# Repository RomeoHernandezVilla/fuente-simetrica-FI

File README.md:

# fuente_simetrica_FI
 HW pininos fuente de alimentacion simetrica

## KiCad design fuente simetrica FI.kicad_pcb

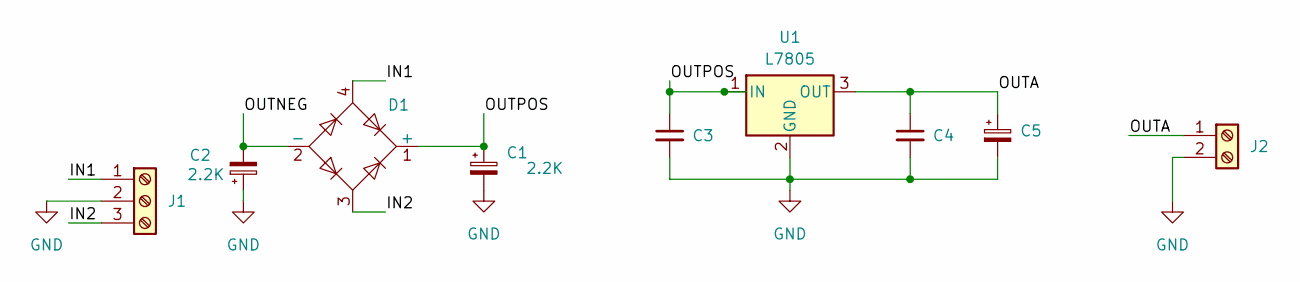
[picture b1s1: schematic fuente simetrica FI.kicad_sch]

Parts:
C1, C2: 2.2K; CP_Radial_D12.5mm_P5.00mm
C3, C4: C_Small; C_Disc_D5.0mm_W2.5mm_P5.00mm
C5: C_Polarized_Small; CP_Radial_D12.5mm_P5.00mm
D1: DF005M; Diode_Bridge_Round_D9.0mm
J1: Screw_Terminal_01x03; TerminalBlock_Phoenix_MKDS-1,5-3-5.08_1x03_P5.08mm_Horizont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
J2: Screw_Terminal_01x02; TerminalBlock_Phoenix_MKDS-1,5-2_1x02_P5.00mm_Horizontal
U1: L7805; TO-220-3_Horizontal_TabDown

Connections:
/IN1: D1.4, J1.1
/IN2: D1.3, J1.3
/OUTA: C4.1, C5.1, J2.1, U1.3 (OUT)
/OUTNEG: C2.2, D1.2 (-)
/OUTPOS: C1.1, C3.1, D1.1 (+), U1.1 (IN)
GND: C1.2, C2.1, C3.2, C4.2, C5.2, J1.2, J2.2, U1.2 (GND)

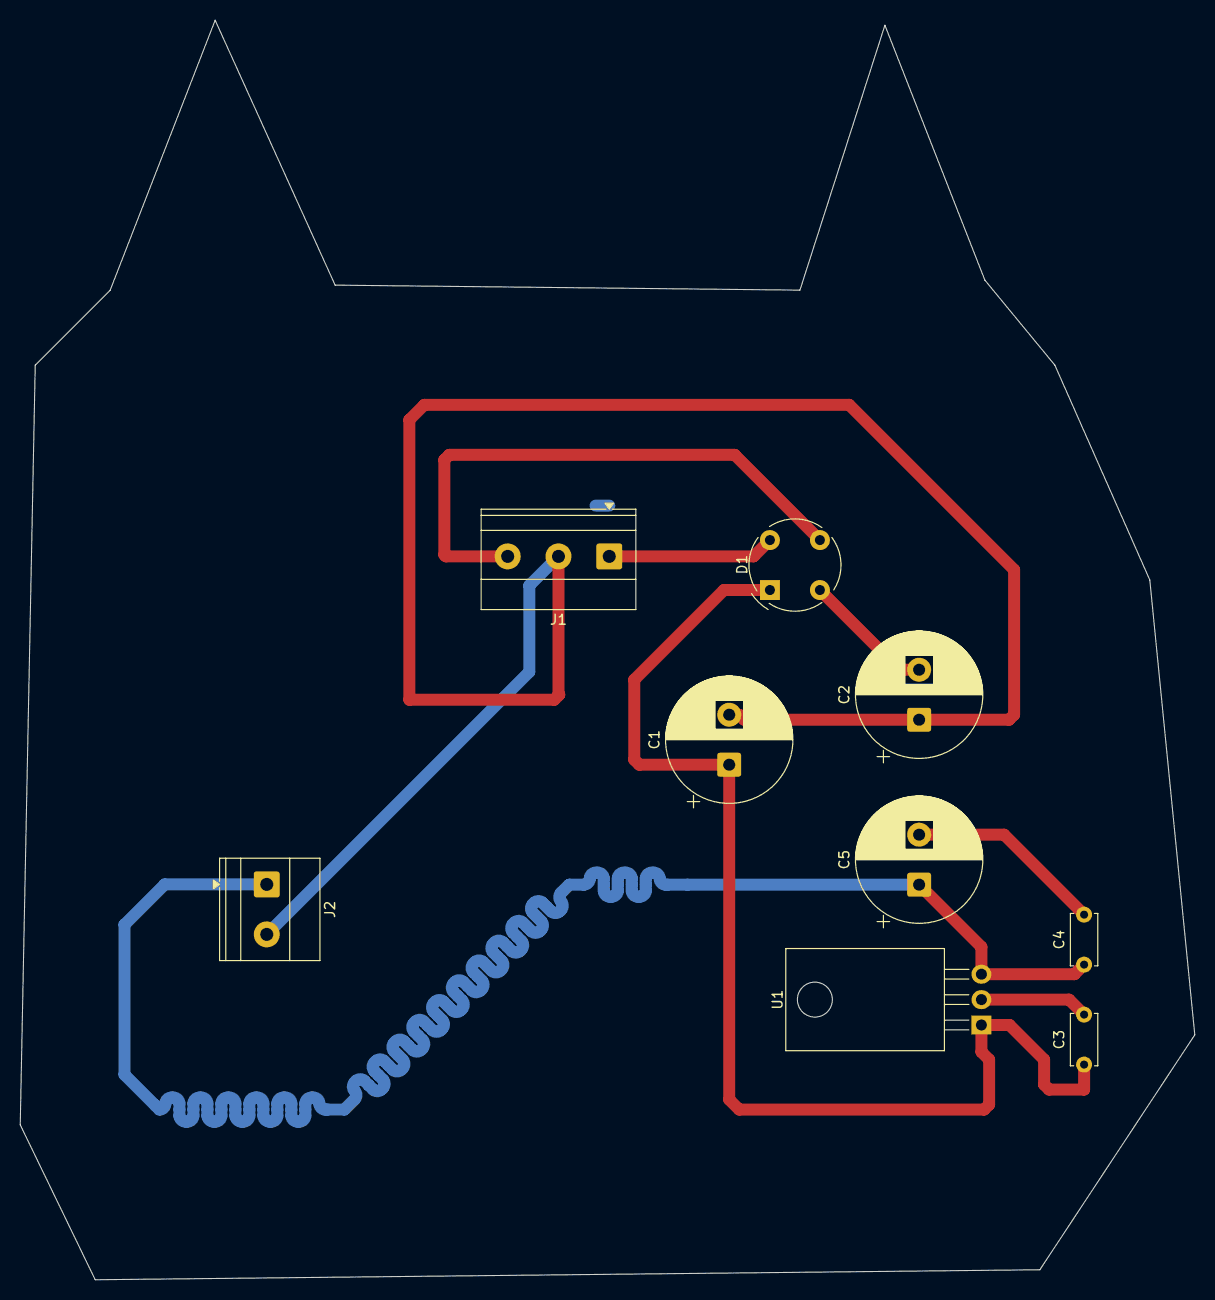
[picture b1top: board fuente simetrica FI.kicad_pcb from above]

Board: 2 copper layers, 117.5 x 126.0 mm, 9 parts (0 on the bottom side), 6 nets.

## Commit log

2026-06-22 agregue .step de la pcb
    gato erizo
2026-06-22 se agrega stl
